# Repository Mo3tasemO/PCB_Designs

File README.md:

# PCB_Designs

Collection of my personal **PCB projects**, breakouts, development boards, and small electronics designs — mostly created in **KiCad**.

Currently includes:

- Breadboard-friendly linear / switching power supplies
- ESP8266 / ESP-12 based development/breakout boards
- Simple function/signal generators
- Various utility/test circuits

<!--
Example how to embed images later:

-->

## ⚡ Want to build something?

1. Open the folder of the project you like
2. Open the `.kicad_pro` file in KiCad
3. Plot Gerbers / Drill files yourself or use the existing `gerbers/` / `production/` folder (if present)
4. Order from your favorite PCB fab 

**Warning:** Most designs here are **not production-tested** yet. You can use it at your own risk.

---

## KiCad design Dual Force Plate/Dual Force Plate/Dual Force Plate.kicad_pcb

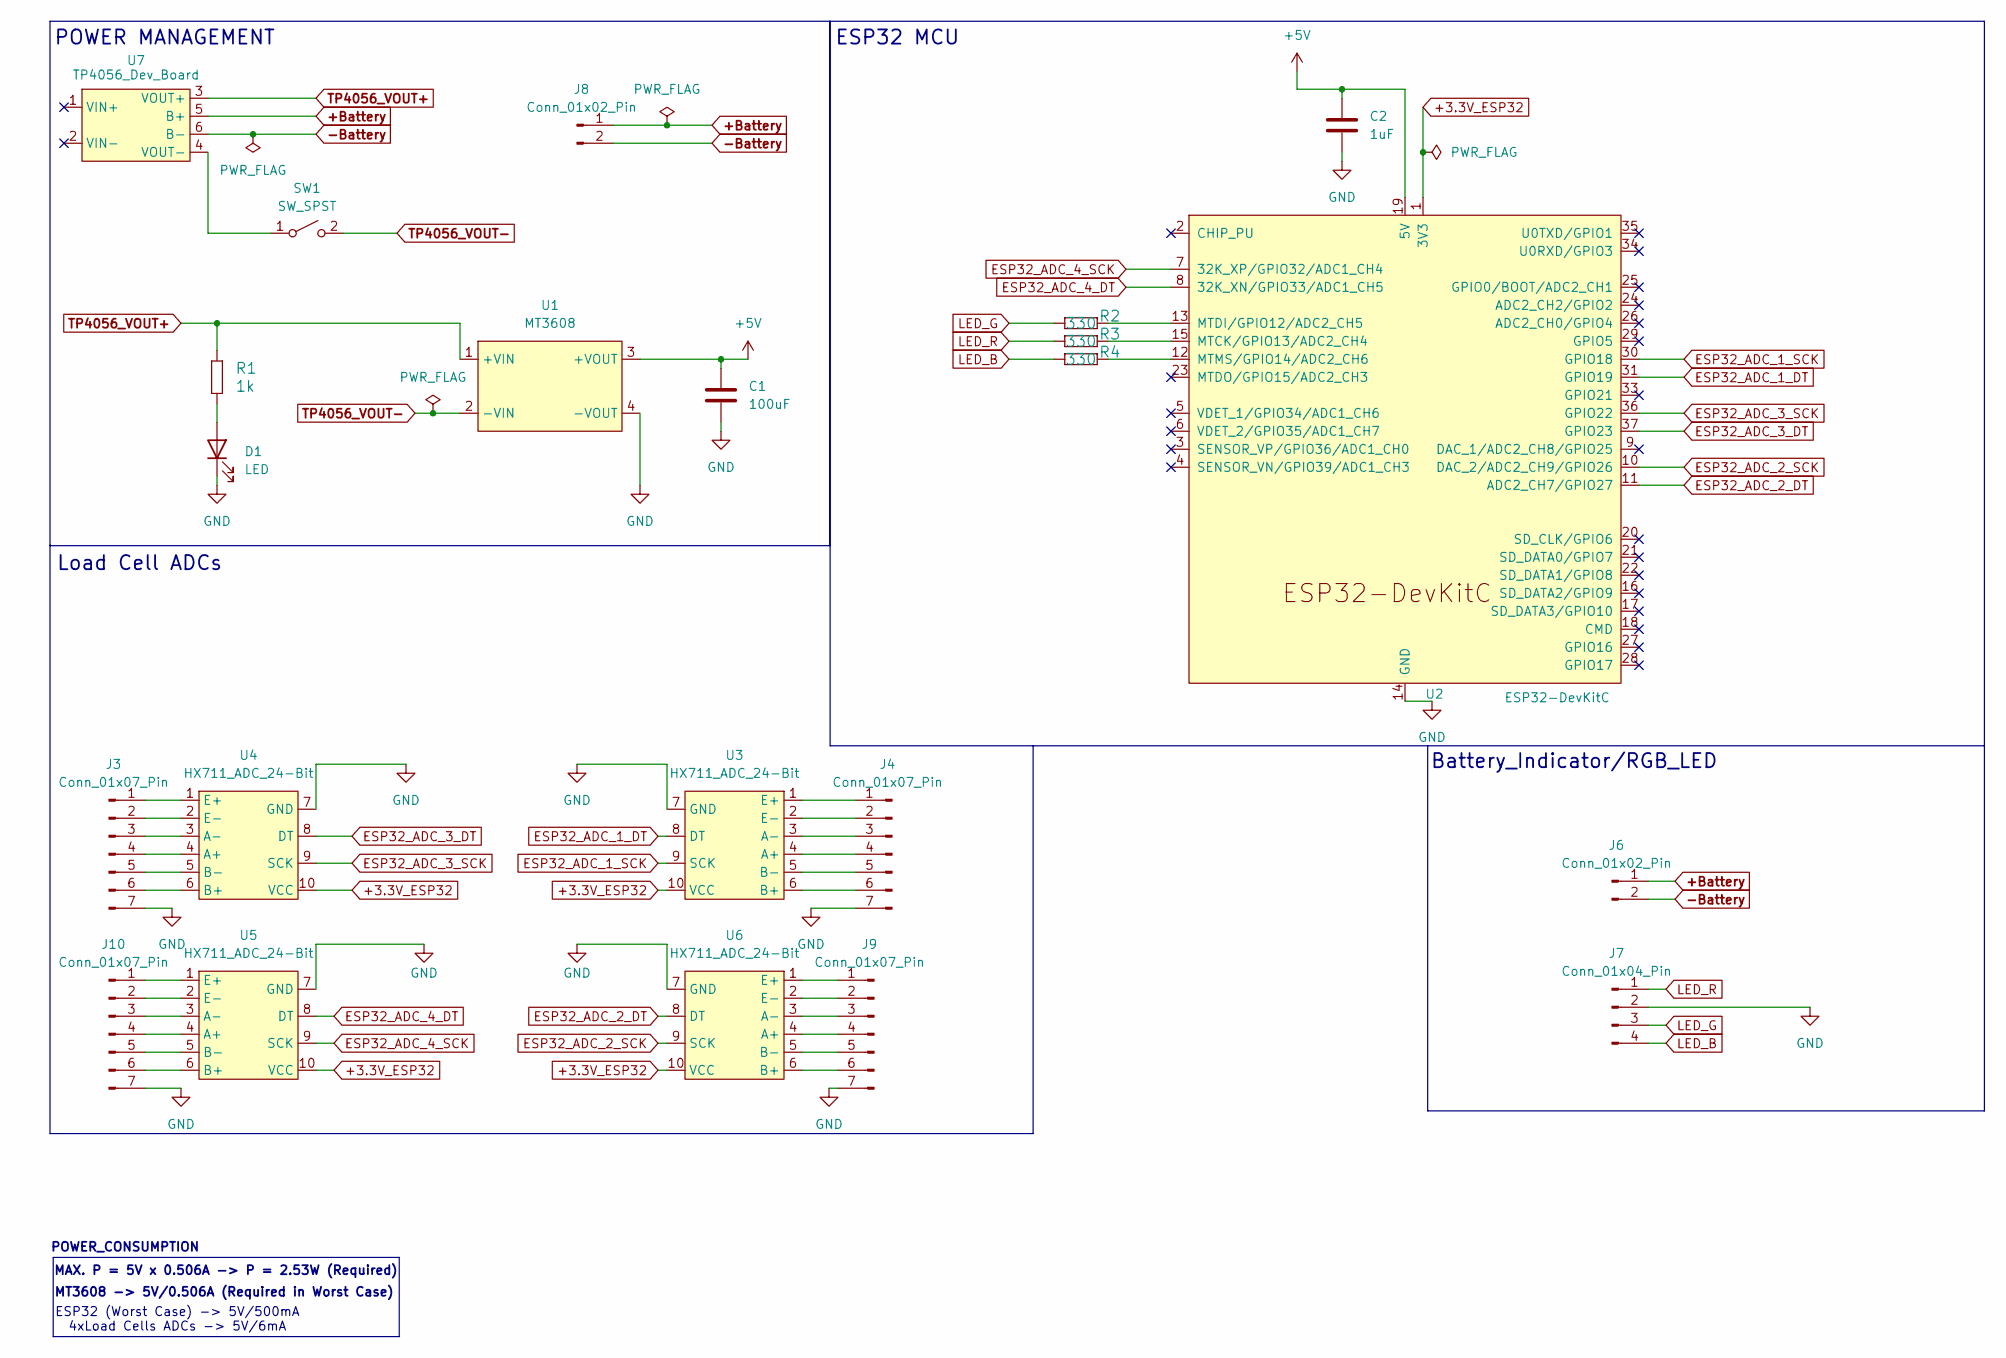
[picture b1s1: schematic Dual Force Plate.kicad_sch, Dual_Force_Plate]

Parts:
C1: 100uF; C_Radial_D6.3mm_H11.0mm_P2.50mm
C2: 1uF; C_Radial_D6.3mm_H11.0mm_P2.50mm
D1: LED; LED_D3.0mm
J3, J4, J9, J10: Conn_01x07_Pin; PinHeader_1x07_P2.54mm_Vertical
J6: Conn_01x02_Pin; PinHeader_1x02_P2.54mm_Vertical
J7: Conn_01x04_Pin; SolderWire-0.5sqmm_1x04_P4.6mm_D0.9mm_OD2.1mm
J8: Conn_01x02_Pin; SolderWire-0.5sqmm_1x02_P4.6mm_D0.9mm_OD2.1mm
R1: 1k; R_Axial_DIN0207_L6.3mm_D2.5mm_P10.16mm_Horizontal
R2, R3, R4: 330; R_Axial_DIN0204_L3.6mm_D1.6mm_P7.62mm_Horizontal
SW1: SW_SPST; PinHeader_1x02_P2.54mm_Vertical
U1: MT3608; MT3608_module
U2: ESP32-DevKitC
U3, U4, U5, U6: HX711_ADC_24-Bit; HX711_Weight-Scale_(ADC)_24-bit
U7: TP4056_Dev_Board; TP4056-Module

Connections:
+3.3V_ESP32: U2.1 (3V3), U3.10 (VCC), U4.10 (VCC), U5.10 (VCC), U6.10 (VCC)
+5V: C1.1, C2.1, U1.3 (+VOUT), U2.19 (5V)
+Battery: J6.1, J8.1, U7.5 (B+)
-Battery: J6.2, J8.2, U7.6 (B-)
ESP32_ADC_1_DT: U2.31 (GPIO19), U3.8 (DT)
ESP32_ADC_1_SCK: U2.30 (GPIO18), U3.9 (SCK)
ESP32_ADC_2_DT: U2.11 (ADC2_CH7/GPIO27), U6.8 (DT)
ESP32_ADC_2_SCK: U2.10 (DAC_2/ADC2_CH9/GPIO26), U6.9 (SCK)
ESP32_ADC_3_DT: U2.37 (GPIO23), U4.8 (DT)
ESP32_ADC_3_SCK: U2.36 (GPIO22), U4.9 (SCK)
ESP32_ADC_4_DT: U2.8 (32K_XN/GPIO33/ADC1_CH5), U5.8 (DT)
ESP32_ADC_4_SCK: U2.7 (32K_XP/GPIO32/ADC1_CH4), U5.9 (SCK)
GND: C1.2, C2.2, D1.1 (K), J3.7, J4.7, J7.2, J9.7, J10.7, U1.4 (-VOUT), U2.14 (GND), U2.32 (GND), U2.38 (GND), U3.7 (GND), U4.7 (GND), U5.7 (GND), U6.7 (GND)
LED_B: J7.4, R4.2
LED_G: J7.3, R2.2
LED_R: J7.1, R3.2
unnamed: D1.2 (A), R1.1
unnamed: J3.1, U4.1 (E+)
unnamed: J3.2, U4.2 (E-)
unnamed: J3.3, U4.3 (A-)
unnamed: J3.4, U4.4 (A+)
unnamed: J3.5, U4.5 (B-)
unnamed: J3.6, U4.6 (B+)
unnamed: J4.1, U3.1 (E+)
unnamed: J4.2, U3.2 (E-)
unnamed: J4.3, U3.3 (A-)
unnamed: J4.4, U3.4 (A+)
unnamed: J4.5, U3.5 (B-)
unnamed: J4.6, U3.6 (B+)
unnamed: J9.1, U6.1 (E+)
unnamed: J9.2, U6.2 (E-)
unnamed: J9.3, U6.3 (A-)
unnamed: J9.4, U6.4 (A+)
unnamed: J9.5, U6.5 (B-)
unnamed: J9.6, U6.6 (B+)
unnamed: J10.1, U5.1 (E+)
unnamed: J10.2, U5.2 (E-)
unnamed: J10.3, U5.3 (A-)
unnamed: J10.4, U5.4 (A+)
unnamed: J10.5, U5.5 (B-)
unnamed: J10.6, U5.6 (B+)
unnamed: SW1.1 (A), U7.4 (VOUT-)
unnamed: R3.1, U2.15 (MTCK/GPIO13/ADC2_CH4)
unnamed: R2.1, U2.13 (MTDI/GPIO12/ADC2_CH5)
unnamed: R4.1, U2.12 (MTMS/GPIO14/ADC2_CH6)
TP4056_VOUT+: R1.2, U1.1 (+VIN), U7.3 (VOUT+)
TP4056_VOUT-: SW1.2 (B), U1.2 (-VIN)

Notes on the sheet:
MT3608 -> 5V/0.506A (Required in Worst Case)
ESP32 (Worst Case) -> 5V/500mA 4xLoad Cells ADCs -> 5V/6mA
Load Cell ADCs
ESP32 MCU
Battery_Indicator/RGB_LED
POWER_CONSUMPTION
MAX. P = 5V x 0.506A -> P = 2.53W (Required)
POWER MANAGEMENT

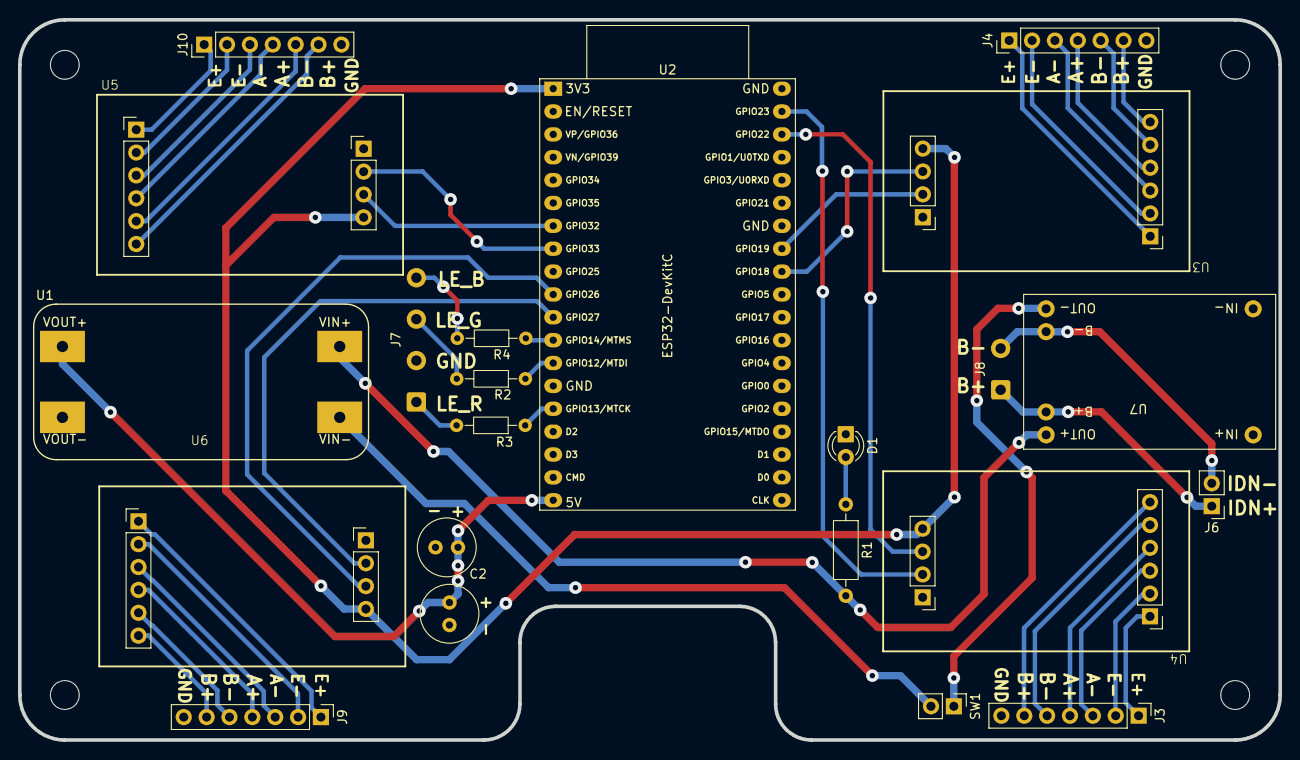
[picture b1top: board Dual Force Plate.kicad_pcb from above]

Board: 2 copper layers, 140.0 x 80.0 mm, 22 parts (0 on the bottom side), 47 nets.

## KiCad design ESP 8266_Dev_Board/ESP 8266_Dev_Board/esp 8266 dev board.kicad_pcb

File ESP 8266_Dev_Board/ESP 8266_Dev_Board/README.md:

# DEV_Board_By_Mo3 (ESP8266-12E)

A custom-designed, high-performance development board based on the **ESP-12E (ESP8266)** module. This board features a modern **USB-C** interface and is designed for seamless prototyping with integrated power regulation and USB-to-TTL conversion.

---

## 🚀 Key Features

* **Core Microcontroller:** ESP8266-12E module with integrated PCB antenna.
* **Modern Interface:** USB-C 16-pin receptacle for power and programming.
* **Stable Power:** AMS1117-3.3V LDO regulator providing consistent 3.3V power from the 5V USB input.
* **USB-to-Serial:** Integrated CH340C bridge chip for plug-and-play serial communication.
* **Protection:** Includes a BZW55B3V3 Zener diode and decoupling capacitors for voltage stability and ESD protection.
* **Manual Controls:** Dedicated Flash (DTR/RTS logic) and Reset (SW_SPST) buttons for easy bootloader access.

---

## 🛠 Hardware Architecture

The board is logically divided into four main sections as defined in the schematics:

| Section | Components | Purpose |
| :--- | :--- | :--- |
| **Source** | AMS1117-3.3, BZW55B3V3, C1, C3 | Voltage regulation and power filtering. |
| **USB** | USB-C 16P, D2 Diode, C6 | Power input and basic surge protection. |
| **USB to TTL** | CH340C, C4, C5, R4, R5 | Bridge between PC USB and ESP8266 UART. |
| **ESP8266** | ESP-12E, Reset/Flash Switch, I/O Headers | Main processing, GPIO breakout, and boot mode selection. |

---

## 📐 Pinout & Connectivity

The board breaks out all essential GPIOs via two main headers:

* **Header J3:** GPIO12, GPIO13, GPIO14, GPIO15, GPIO16, and GND.
* **Header J4:** RESET, SCK, MOSI, MISO, and GND.
* **Header J5:** ADC and various ID pins for expanded peripheral support.

---

## 🖥️ Setup and Programming

1. **Driver Installation:** Ensure the **CH340 drivers** are installed on your computer.
2. **Arduino IDE Configuration:** * Add the ESP8266 board URL to your preferences.
   * Select **"NodeMCU 1.0 (ESP-12E Module)"** or **"Generic ESP8266 Module"**.
3. **Flashing:** Use the USB-C cable to connect to your PC. The board features an auto-reset circuit (DTR/RTS) for automatic flashing, but manual buttons are available if needed.

---

## 🖼️ Gallery

### 2D Layout & Routing
  
*Double-layer design with optimized ground pours for RF stability.*

### 3D Render

*Fully assembled view showing component placement and compact form factor.*

---

## 📜 License

This project is open-source. Feel free to use, modify, and distribute it for your own IoT applications.

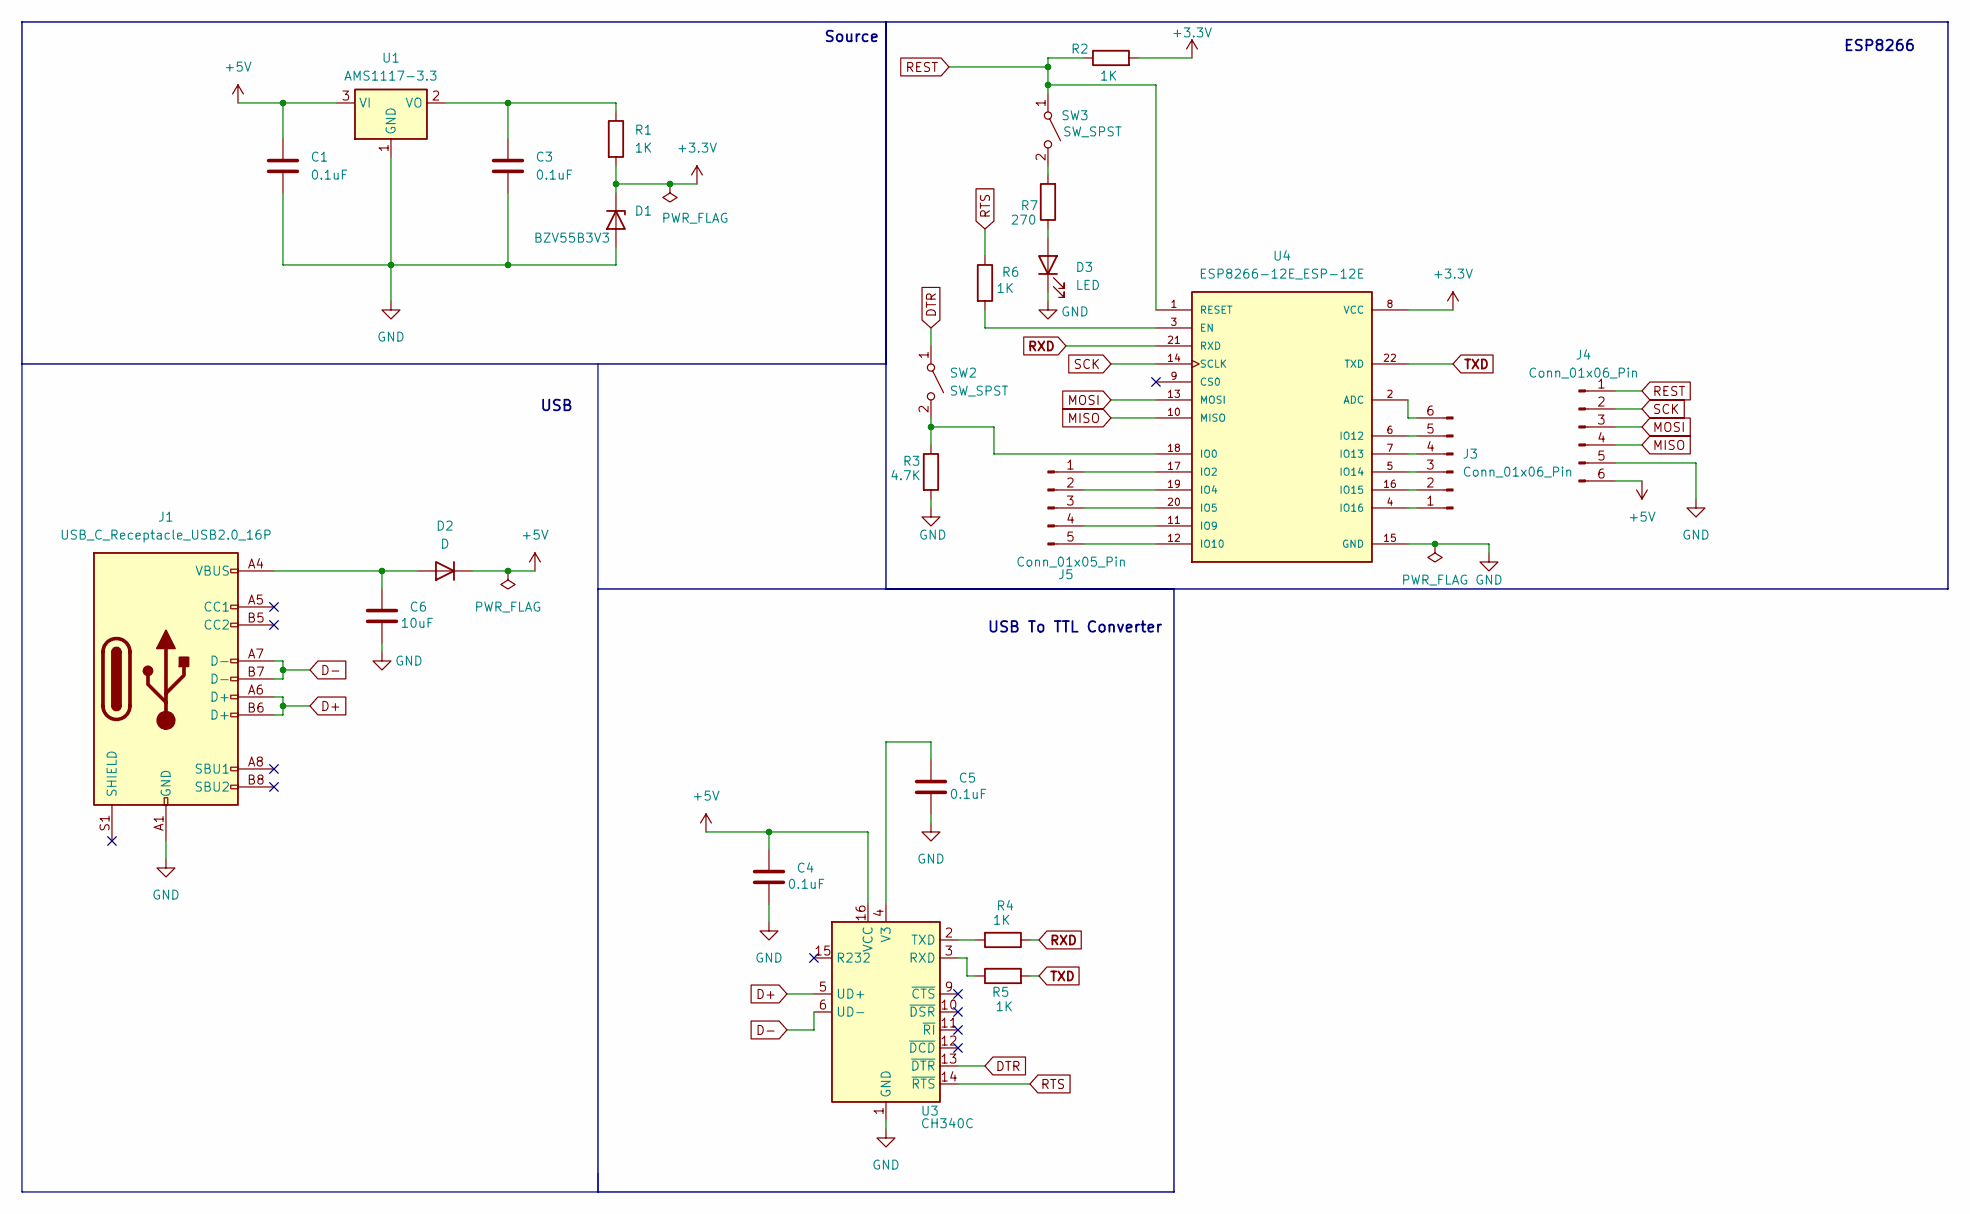
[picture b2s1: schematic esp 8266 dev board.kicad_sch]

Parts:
C1, C3, C4, C5: 0.1uF; C_0603_1608Metric
C6: 10uF; CP_Elec_4x4.5
D1: BZV55B3V3; D_MiniMELF
D2: D; SOD-123
D3: LED; LED_0603_1608Metric_Red
J1: USB_C_Receptacle_USB2.0_16P; USB_C_Receptacle_GCT_USB4105-xx-A_16P_TopMnt_Horizontal
J3, J4: Conn_01x06_Pin; PinHeader_1x06_P2.54mm_Vertical
J5: Conn_01x05_Pin; PinHeader_1x05_P2.54mm_Vertical
R1, R2, R4, R5, R6: 1K; R_1206_3216Metric
R3: 4.7K; R_0805_2012Metric
R7: 270; R_0603_1608Metric
SW2, SW3: SW_SPST; Push_SMD_6x3.5mm
U1: AMS1117-3.3; SOT-223-3_TabPin2
U3: CH340C; SOIC-16_3.9x9.9mm_P1.27mm
U4: ESP8266-12E_ESP-12E; XCVR_ESP8266-12E_ESP-12E

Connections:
+3.3V: D1.1 (K), R1.2, R2.2, U4.8 (VCC)
+5V: C1.1, C4.1, D2.1 (K), J4.6, U1.3 (VI), U3.16 (VCC)
D+: J1.A6 (D+), J1.B6 (D+), U3.5 (UD+)
D-: J1.A7 (D-), J1.B7 (D-), U3.6 (UD-)
DTR: SW2.1 (A), U3.13 (~DTR)
GND: C1.2, C3.2, C4.2, C5.2, C6.2, D1.2 (A), D3.1 (K), J1.A1 (GND), J1.A12 (GND), J1.B1 (GND), J1.B12 (GND), J4.5, R3.2, U1.1 (GND), U3.1 (GND), U4.15 (GND)
MISO: J4.4, U4.10 (MISO)
MOSI: J4.3, U4.13 (MOSI)
unnamed: C6.1, D2.2 (A), J1.A4 (VBUS), J1.A9 (VBUS), J1.B4 (VBUS), J1.B9 (VBUS)
unnamed: D3.2 (A), R7.1
unnamed: J3.1, U4.4 (IO16)
unnamed: J3.2, U4.16 (IO15)
unnamed: J3.3, U4.5 (IO14)
unnamed: J3.4, U4.7 (IO13)
unnamed: J3.5, U4.6 (IO12)
unnamed: J3.6, U4.2 (ADC)
unnamed: J5.1, U4.17 (IO2)
unnamed: J5.2, U4.19 (IO4)
unnamed: J5.3, U4.20 (IO5)
unnamed: J5.4, U4.11 (IO9)
unnamed: J5.5, U4.12 (IO10)
unnamed: R3.1, SW2.2 (B), U4.18 (IO0)
unnamed: R7.2, SW3.2 (B)
unnamed: C3.1, R1.1, U1.2 (VO)
unnamed: R5.1, U3.3 (RXD)
unnamed: R4.2, U3.2 (TXD)
unnamed: C5.1, U3.4 (V3)
unnamed: R6.2, U4.3 (EN)
REST: J4.1, R2.1, SW3.1 (A), U4.1 (RESET)
RTS: R6.1, U3.14 (~RTS)
RXD: R4.1, U4.21 (RXD)
SCK: J4.2, U4.14 (SCLK)
TXD: R5.2, U4.22 (TXD)

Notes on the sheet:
USB To TTL Converter
USB
Source
ESP8266

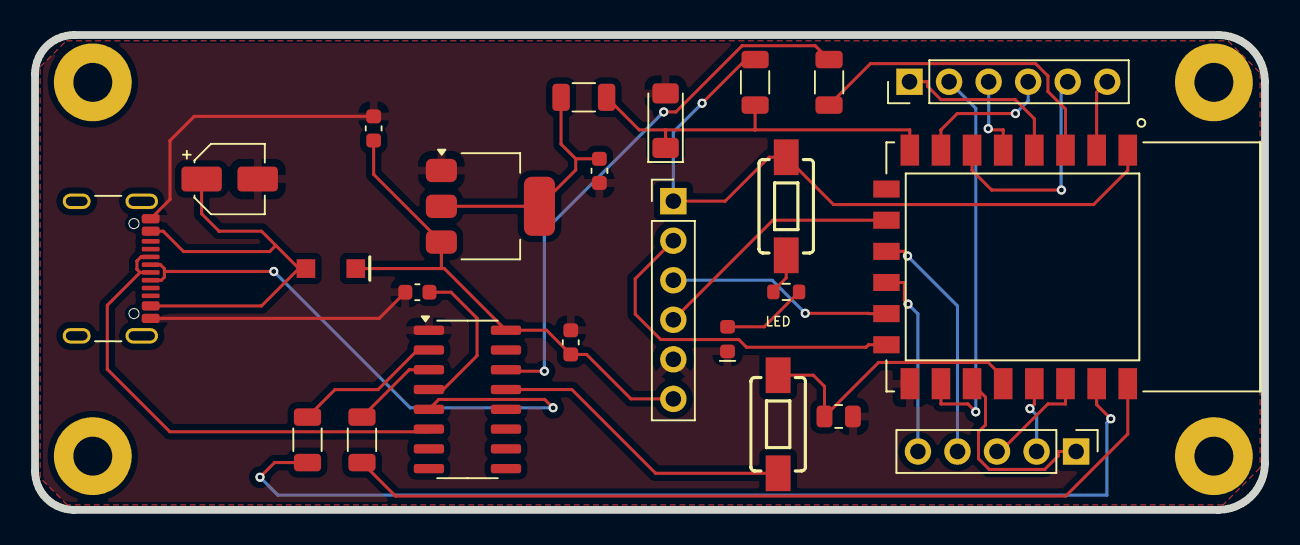
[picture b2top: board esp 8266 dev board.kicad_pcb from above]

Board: 2 copper layers, 79.0 x 30.5 mm, 24 parts (0 on the bottom side), 33 nets.

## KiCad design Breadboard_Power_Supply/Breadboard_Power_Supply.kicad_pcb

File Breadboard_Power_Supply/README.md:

# 🔌 Breadboard Power Supply Module (5V / 3.3V)

A compact and reliable **breadboard power supply module** that provides **regulated 5V and 3.3V outputs** from a 12V DC input.  
This project is designed for electronics prototyping, embedded systems development, and educational applications.

---

## 📖 Overview

This board converts a 12V DC input into stable 5V and 3.3V power rails using linear voltage regulators.  
It is optimized to plug directly into a standard breadboard, allowing quick and safe powering of microcontrollers, sensors, and peripheral circuits during development and testing.

---

## ⚙️ Features

- 12V DC input via barrel jack  
- Regulated **5V output using LM7805**  
- Regulated **3.3V output using LM317**  
- Jumper-based voltage selection (5V / 3.3V)  
- Reverse polarity protection diode  
- Power ON LED indicator  
- Breadboard-compatible pin headers  
- Screw terminal outputs for external connections  

---

## 🧠 Circuit Description

- The **LM7805** regulator provides a fixed 5V output with input and output decoupling capacitors to ensure voltage stability.  
- The **LM317** adjustable regulator is configured to output 3.3V using a resistor divider network.  
- A protection diode prevents damage caused by incorrect input polarity.  
- An LED with a current-limiting resistor indicates when the board is powered.

---

## 🛠️ Tools & Components

- **EDA Software:** KiCad  
- **Voltage Regulators:** LM7805, LM317  
- **Input Connector:** DC Barrel Jack  
- **Outputs:** Pin headers and screw terminals  

---

## 🚀 Applications

- Breadboard prototyping  
- Powering Arduino, STM32, ESP32, and AVR projects  
- Embedded systems testing  
- Educational electronics labs  

---
### 2D Layout & Routing

### 3D Render

## 📂 Project Structure

```text
├── Schematic/
├── PCB/
├── 3D_View/
├── Images/
└── README.md

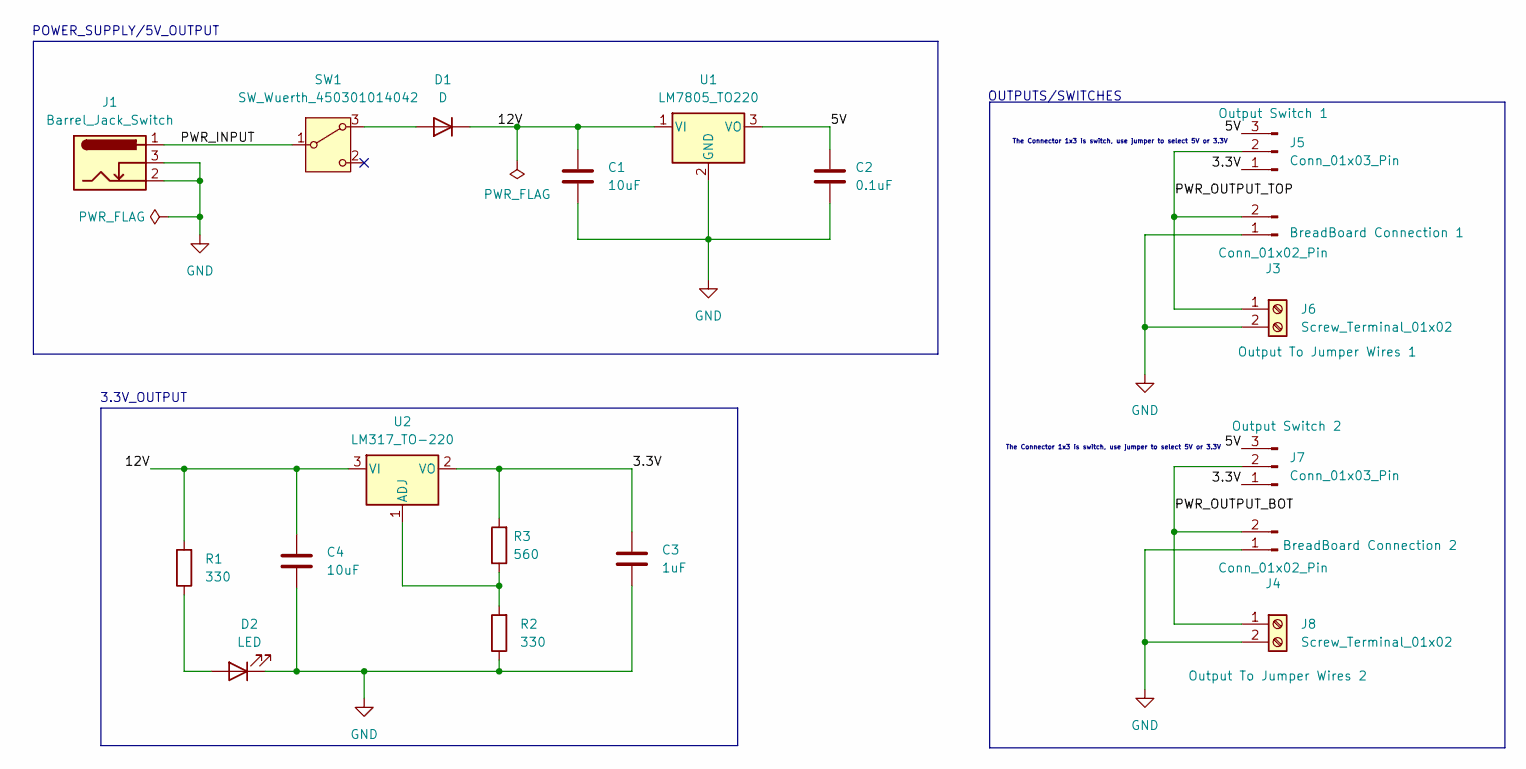
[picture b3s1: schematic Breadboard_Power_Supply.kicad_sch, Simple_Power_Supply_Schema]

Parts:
C1, C4: 10uF; C_Disc_D5.0mm_W2.5mm_P2.50mm
C2: 0.1uF; C_Disc_D5.0mm_W2.5mm_P2.50mm
C3: 1uF; C_Disc_D5.0mm_W2.5mm_P2.50mm
D1: D; D_5W_P12.70mm_Horizontal
D2: LED; LED_D3.0mm
J1: Barrel_Jack_Switch; BarrelJack_Horizontal
J3, J4: Conn_01x02_Pin; PinHeader_1x02_P2.54mm_Vertical
J5, J7: Conn_01x03_Pin; PinHeader_1x03_P2.54mm_Vertical
J6, J8: Screw_Terminal_01x02; TerminalBlock_Phoenix_MKDS-1,5-2_1x02_P5.00mm_Horizontal
R1, R2: 330; R_Axial_DIN0204_L3.6mm_D1.6mm_P7.62mm_Horizontal
R3: 560; R_Axial_DIN0204_L3.6mm_D1.6mm_P7.62mm_Horizontal
SW1: SW_Wuerth_450301014042; SW_Slide-03_Wuerth-WS-SLTV_10x2.5x6.4_P2.54mm
U1: LM7805_TO220; TO-220-3_Vertical
U2: LM317_TO-220; TO-220-3_Vertical

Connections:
/3.3V: C3.1, J5.1, J7.1, R3.2, U2.2 (VO)
/5V: C2.1, J5.3, J7.3, U1.3 (VO)
/12V: C1.1, C4.1, D1.1 (K), R1.2, U1.1 (VI), U2.3 (VI)
/PWR_INPUT: J1.1, SW1.1 (B)
/PWR_OUTPUT_BOT: J4.2, J7.2, J8.1
/PWR_OUTPUT_TOP: J3.2, J5.2, J6.1
GND: C1.2, C2.2, C3.2, C4.2, D2.1 (K), J1.2, J1.3, J3.1, J4.1, J6.2, J8.2, R2.1, U1.2 (GND)
unnamed: D1.2 (A), SW1.3 (A)
unnamed: D2.2 (A), R1.1
unnamed: R2.2, R3.1, U2.1 (ADJ)

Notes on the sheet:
The Connector 1x3 is switch, use jumper to select 5V or 3.3V
3.3V_OUTPUT
OUTPUTS/SWITCHES
POWER_SUPPLY/5V_OUTPUT

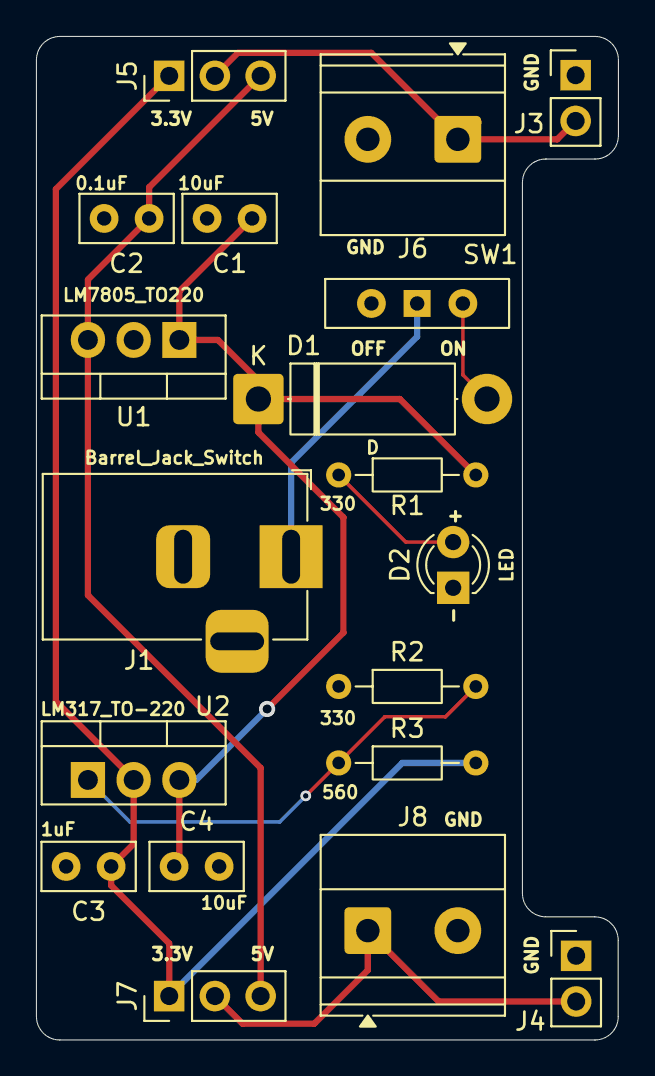
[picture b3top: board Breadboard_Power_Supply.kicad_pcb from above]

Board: 2 copper layers, 32.3 x 55.8 mm, 19 parts (0 on the bottom side), 10 nets.

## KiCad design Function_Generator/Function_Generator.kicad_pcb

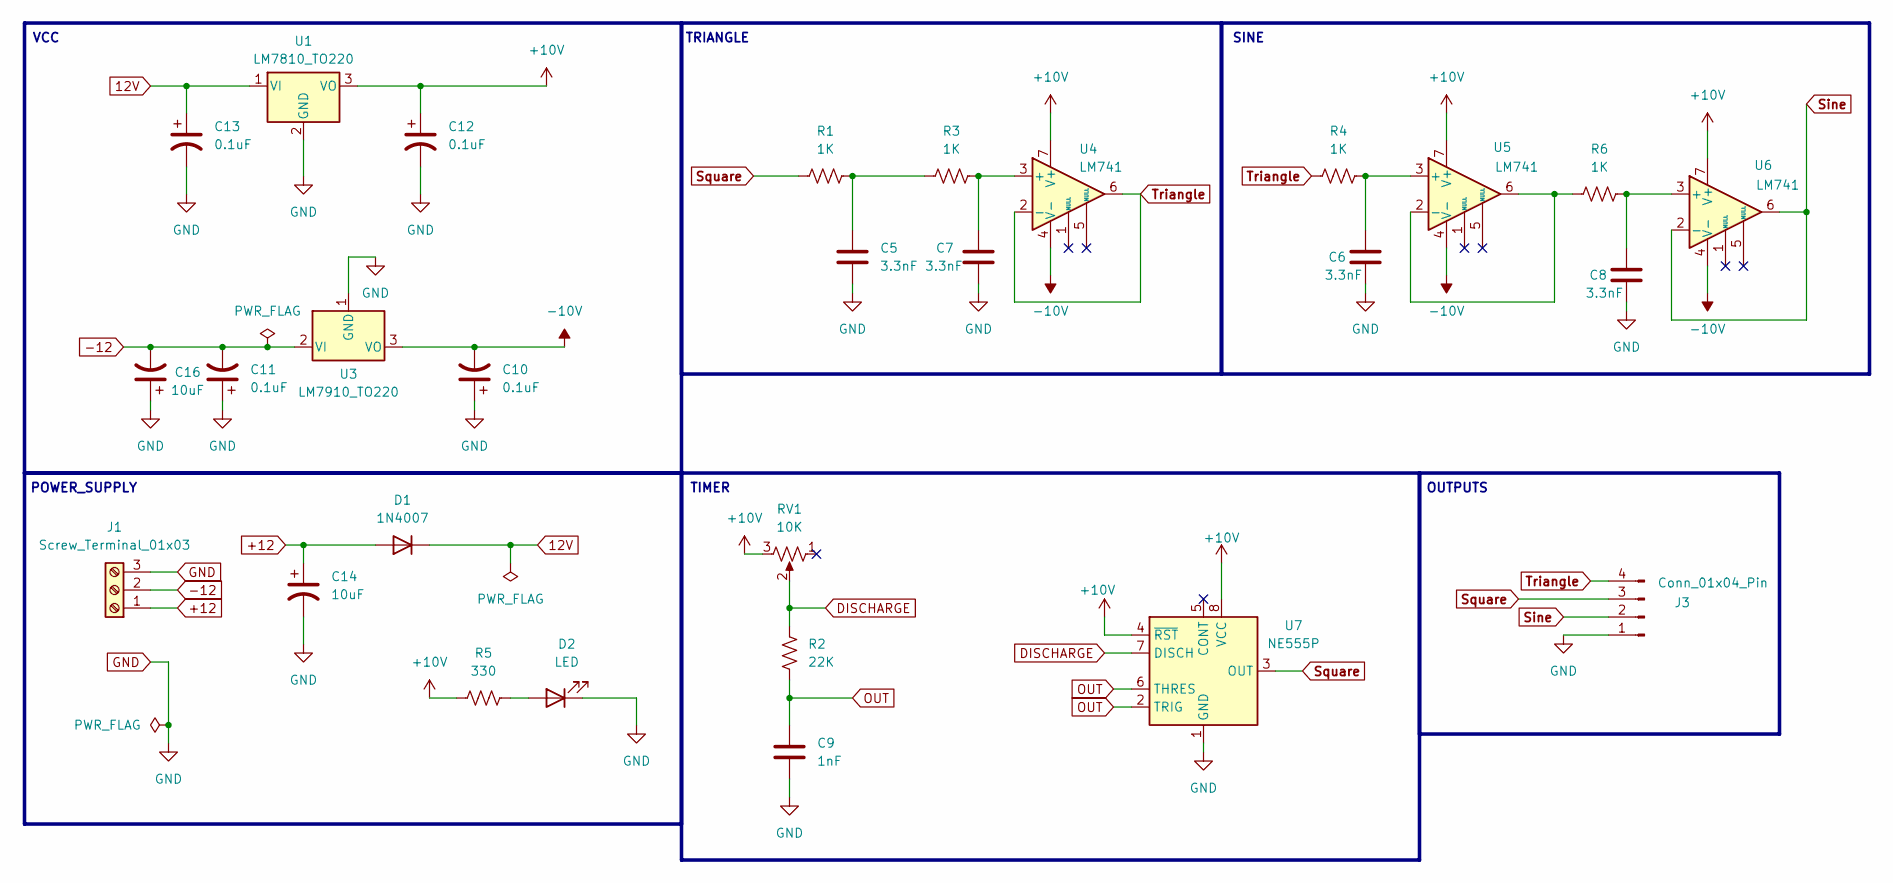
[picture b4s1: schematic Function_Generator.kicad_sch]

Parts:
C5, C6, C7, C8: 3.3nF; C_Disc_D5.0mm_W2.5mm_P5.00mm
C9: 1nF; C_Disc_D5.0mm_W2.5mm_P5.00mm
C10, C11, C12, C13: 0.1uF; CP_Radial_D8.0mm_P3.50mm
C14, C16: 10uF; CP_Radial_D8.0mm_P3.50mm
D1: 1N4007; D_A-405_P10.16mm_Horizontal
D2: LED; LED_D3.0mm
J1: Screw_Terminal_01x03; TerminalBlock_Phoenix_PT-1,5-3-5.0-H_1x03_P5.00mm_Horizontal
J3: Conn_01x04_Pin; PinHeader_1x04_P2.00mm_Vertical
R1, R3, R4, R6: 1K; R_Axial_DIN0207_L6.3mm_D2.5mm_P10.16mm_Horizontal
R2: 22K; R_Axial_DIN0207_L6.3mm_D2.5mm_P10.16mm_Horizontal
R5: 330; R_Axial_DIN0207_L6.3mm_D2.5mm_P10.16mm_Horizontal
RV1: 10K; Rotary Potentiometer_Horizontal
U1: LM7810_TO220; TO-220-3_Vertical
U3: LM7910_TO220; TO-220-3_Vertical
U4, U5, U6: LM741; LM741CN_NOPB
U7: NE555P; DIP-8_W7.62mm

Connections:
12V: C13.1, D1.1 (K), U1.1 (VI)
+10V: C12.1, R5.1, RV1.3, U1.3 (VO), U4.7 (V+), U5.7 (V+), U6.7 (V+), U7.4 (~RST), U7.8 (VCC); also elsewhere on the board
+12: C14.1, D1.2 (A), J1.1
-10V: C10.2, U3.3 (VO), U4.4 (V-), U5.4 (V-), U6.4 (V-)
-12: C11.2, C16.2, J1.2, U3.2 (VI)
DISCHARGE: R2.1, RV1.2, U7.7 (DISCH); also elsewhere on the board
GND: C5.2, C6.2, C7.2, C8.2, C9.2, C10.1, C11.1, C12.2, C13.2, C14.2, C16.1, D2.1 (K), J1.3, J3.1, U1.2 (GND), U3.1 (GND), U7.1 (GND); also elsewhere on the board
unnamed: C5.1, R1.1, R3.2
unnamed: D2.2 (A), R5.2
unnamed: C7.1, R3.1, U4.3 (+)
unnamed: C6.1, R4.2, U5.3 (+)
unnamed: R6.1, U5.2 (-), U5.6
unnamed: C8.1, R6.2, U6.3 (+)
OUT: C9.1, R2.2, U7.2 (TRIG), U7.6 (THRES); also elsewhere on the board
Sine: J3.2, U6.2 (-), U6.6
Square: J3.3, R1.2, U7.3 (OUT); also elsewhere on the board
Triangle: J3.4, R4.1, U4.2 (-), U4.6

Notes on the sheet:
TRIANGLE
POWER_SUPPLY
TIMER
VCC
OUTPUTS
SINE

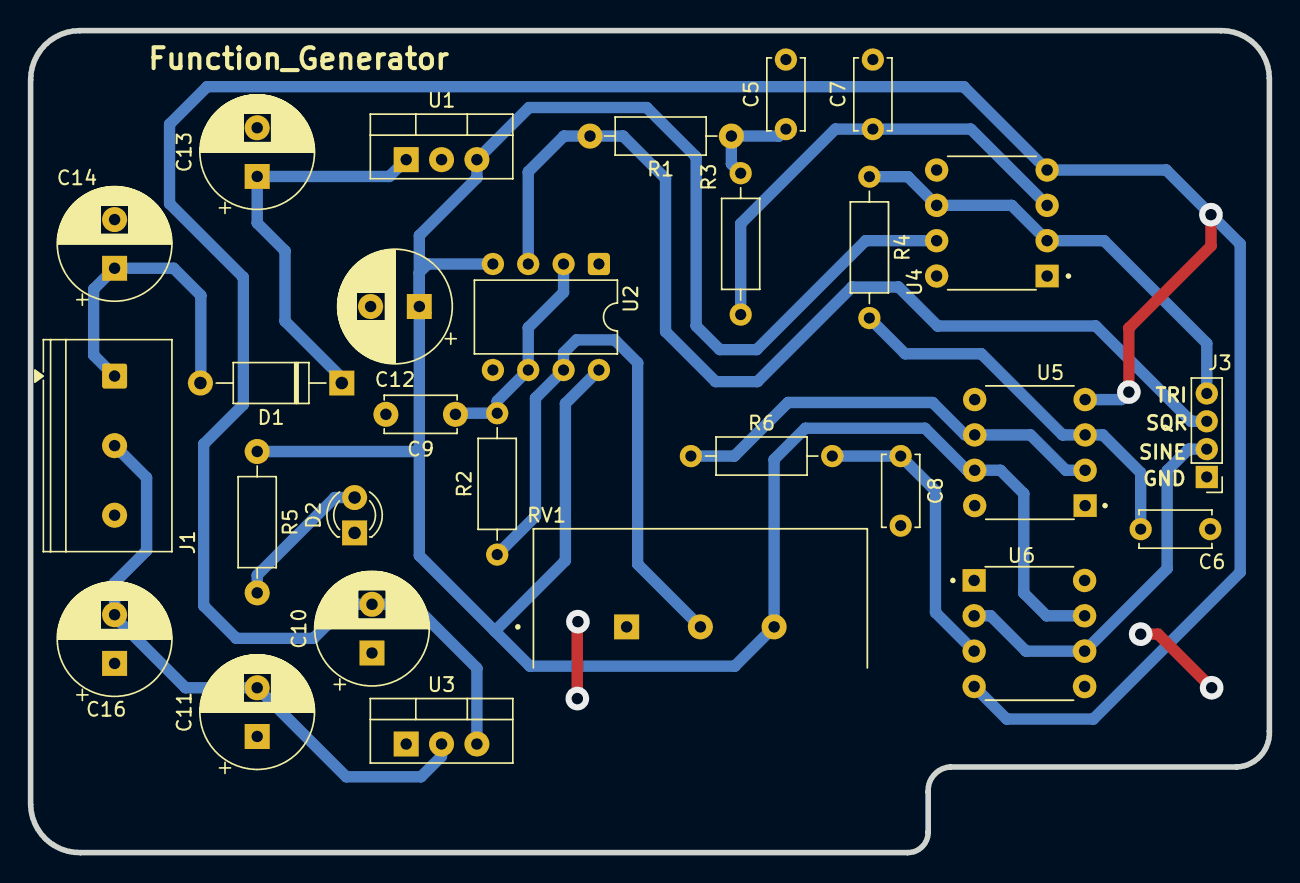
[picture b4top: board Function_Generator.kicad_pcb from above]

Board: 2 copper layers, 89.0 x 59.1 mm, 28 parts (0 on the bottom side), 17 nets.

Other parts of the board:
U2: NE555P; DIP-8_W7.62mm

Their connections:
+10V: U2.4 (R), U2.8 (VCC); also elsewhere on the board
DISCHARGE: U2.7 (DIS); also elsewhere on the board
GND: U2.1 (GND); also elsewhere on the board
OUT: U2.2 (TR), U2.6 (THR); also elsewhere on the board
Square: U2.3 (Q); also elsewhere on the board

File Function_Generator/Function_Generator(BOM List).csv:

"Reference","Qty","Value","DNP","Exclude from BOM","Exclude from Board","Vendor","Link"
"C5,C6,C7,C8","4","3.3nF","","","","Lampatronics","https://lampatronics.com/product/ceramic-capacitors-3-3nf-50v/"
"C10,C11,C12,C13","4","0.1uF","","","","RAM","https://www.ram-e-shop.com/shop/c-0-1u50v-capacitor-0-1uf-50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"
"C14,C16","2","10uF","","","","RAM","https://www.ram-e-shop.com/shop/c-10u100v-capacitor-10uf-100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"
"C15","1","1nF","","","","Lampatronics","https://lampatronics.com/product/ceramic-capacitors-1nf-50v-102/"
"D1","1","1N4007","","","","RAM","https://www.ram-e-shop.com/shop/1n4007-1n4007-general-purpos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"
"D2","1","LED","","","","RAM","https://www.ram-e-shop.com/shop/3mm-led-yy-led-3mm-yellow-co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"
"J1","1","Screw_Terminal_01x03","","","","RAM","https://www.ram-e-shop.com/shop/r-4-roseta-3pin-3-pin-pcb-sc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"
"J3","1","Conn_01x04_Pin","","","","RAM","https://www.ram-e-shop.com/shop/ph1-1x40-male-ph1-pin-header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"
"R1,R3,R4,R6","4","1K","","","","RAM","https://www.ram-e-shop.com/shop/carbon-resistance-1-4w-price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"
"R2","1","22K","","","","RAM","https://www.ram-e-shop.com/shop/carbon-resistance-1-4w-price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"
"R5","1","330","","","","RAM","https://www.ram-e-shop.com/shop/carbon-resistance-1-4w-price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"
"RV1","1","10K","","","","RAM","https://www.ram-e-shop.com/shop/pot-10k-metal-rotary-potenti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"
"U1","1","LM7810_TO220","","","","RAM","https://www.ram-e-shop.com/shop/7810-l7810cv-original-st-5562"
"U2","1","NE555P","","","","RAM","https://www.ram-e-shop.com/shop/ne555-copy-ne555p-timer-ic-c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"
"U3","1","LM7910_TO220","","","","Lampatronics","https://lampatronics.com/product/l7910cv-negative-voltage-re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"
"U4,U5,U6","3","LM741","","","","RAM","https://www.ram-e-shop.com/shop/u741-original-ua741cp-original-5727"

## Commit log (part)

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2026-02-03 Breadboard_Power_Supply_V2
2026-02-03 README File Added
2026-02-03 Update README File
2026-02-03 Update Readme file
    Added project details and usage instructions to README.
2026-05-25 Dual Force Plate Project
2026-06-06 Edit the Layout of (DUAL_FORCE_PLATE)
2026-06-06 Added Mixed Signal Board Project
